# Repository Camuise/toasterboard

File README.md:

# Toasterboard

My attempt at making an open-source Breadboard Companion-like dev board.

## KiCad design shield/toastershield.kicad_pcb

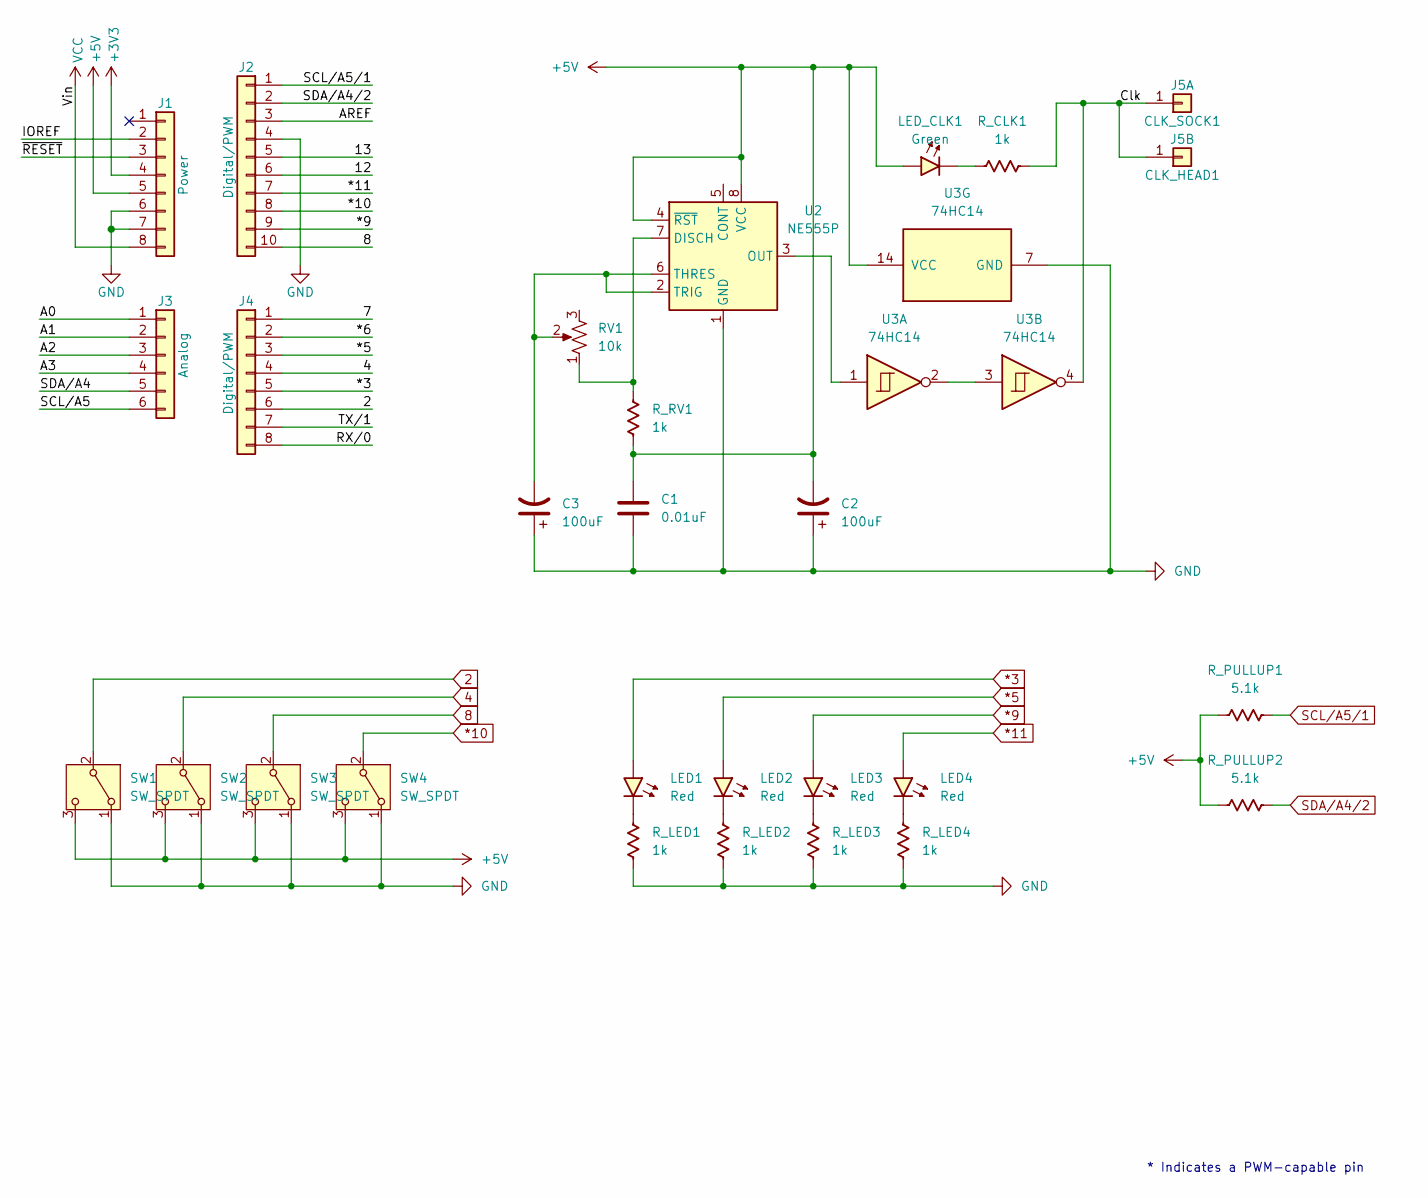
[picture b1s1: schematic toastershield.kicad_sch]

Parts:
C1: 0.01uF; C_Disc_D5.0mm_W2.5mm_P5.00mm
C2, C3: 100uF; CP_Radial_D5.0mm_P2.00mm
CLK_HEAD1: J5B; PinHeader_1x01_P2.54mm_Vertical
CLK_SOCK1: J5A; PinSocket_1x01_P2.54mm_Vertical
J1: Power; PinSocket_1x08_P2.54mm_Vertical
J2: Digital/PWM; PinSocket_1x10_P2.54mm_Vertical
J3: Analog; PinSocket_1x06_P2.54mm_Vertical
J4: Digital/PWM; PinSocket_1x08_P2.54mm_Vertical
LED1, LED2, LED3, LED4: Red; LED_D3.0mm
LED_CLK1: Green; LED_D3.0mm
RV1: 10k; Potentiometer_Piher_PT-15-V02_Vertical
R_CLK1: 1k; R_Axial_DIN0207_L6.3mm_D2.5mm_P2.54mm_Vertical
R_LED1, R_LED2, R_LED3, R_LED4: 1k; R_Axial_DIN0207_L6.3mm_D2.5mm_P2.54mm_Vertical
R_PULLUP1, R_PULLUP2: 5.1k; R_Axial_DIN0207_L6.3mm_D2.5mm_P2.54mm_Vertical
R_RV1: 1k; R_Axial_DIN0207_L6.3mm_D2.5mm_P5.08mm_Vertical
SW1, SW2, SW3, SW4: SW_SPDT; SW_Slide_SPDT_Straight_CK_OS102011MS2Q
U2: NE555P; DIP-8_W7.62mm_Socket
U3: 74HC14; DIP-14_W7.62mm_Socket

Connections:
2: J4.6, SW1.2 (B)
4: J4.4, SW2.2 (B)
8: J2.10, SW3.2 (B)
*3: J4.5, LED1.2 (A)
*5: J4.3, LED2.2 (A)
*9: J2.9, LED3.2 (A)
*10: J2.8, SW4.2 (B)
*11: J2.7, LED4.2 (A)
+3V3: J1.4
+5V: C1.1, C2.2, J1.5, LED_CLK1.2 (A), R_PULLUP1.1, R_PULLUP2.1, R_RV1.2, SW1.3 (C), SW2.3 (C), SW3.3 (C), SW4.3 (C), U2.4 (~RST), U2.8 (VCC), U3.14 (VCC)
/7: J4.1
/12: J2.6
/13: J2.5
/*6: J4.2
/A0: J3.1
/A1: J3.2
/A2: J3.3
/A3: J3.4
/AREF: J2.3
/Clk: CLK_HEAD1.1 (Pin_1_1), CLK_SOCK1.1 (Pin_1_1), R_CLK1.2, U3.4
/IOREF: J1.2
/RX/0: J4.8
/SCL/A5: J3.6
/SDA/A4: J3.5
/TX/1: J4.7
/~RESET: J1.3
GND: C1.2, C2.1, C3.1, J1.6, J1.7, J2.4, R_LED1.2, R_LED2.2, R_LED3.2, R_LED4.2, SW1.1 (A), SW2.1 (A), SW3.1 (A), SW4.1 (A), U2.1 (GND), U3.7 (GND)
unnamed: LED1.1 (K), R_LED1.1
unnamed: LED2.1 (K), R_LED2.1
unnamed: LED3.1 (K), R_LED3.1
unnamed: LED4.1 (K), R_LED4.1
unnamed: LED_CLK1.1 (K), R_CLK1.1
unnamed: RV1.1, R_RV1.1, U2.7 (DISCH)
unnamed: U2.3 (OUT), U3.1
unnamed: C3.2, RV1.2, U2.2 (TRIG), U2.6 (THRES)
unnamed: U3.2, U3.3
SCL/A5/1: J2.1, R_PULLUP1.2
SDA/A4/2: J2.2, R_PULLUP2.2
VCC: J1.8

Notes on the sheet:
* Indicates a PWM-capable pin

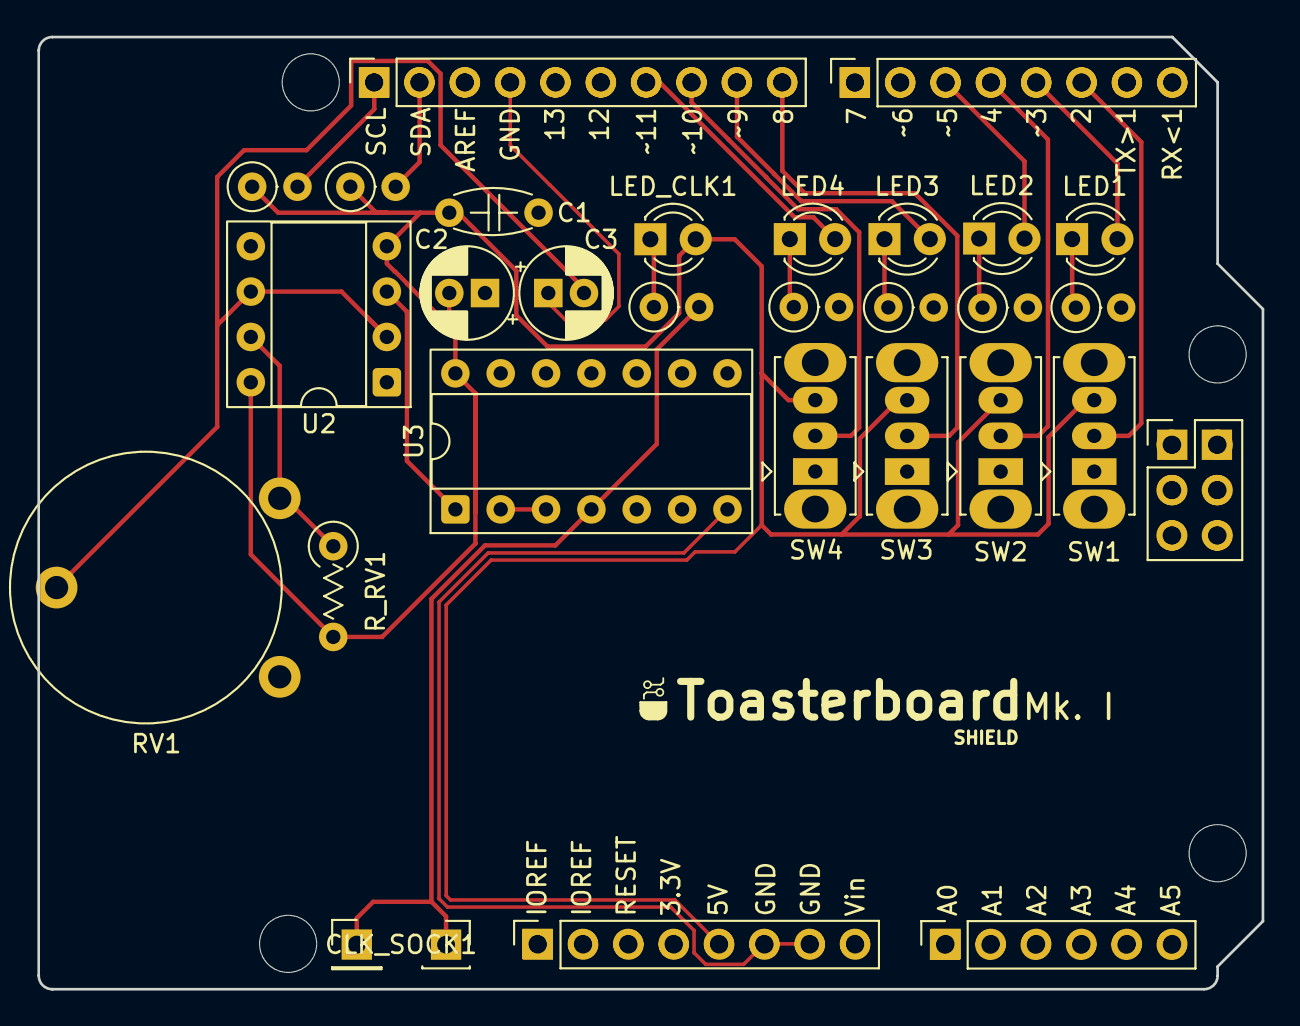
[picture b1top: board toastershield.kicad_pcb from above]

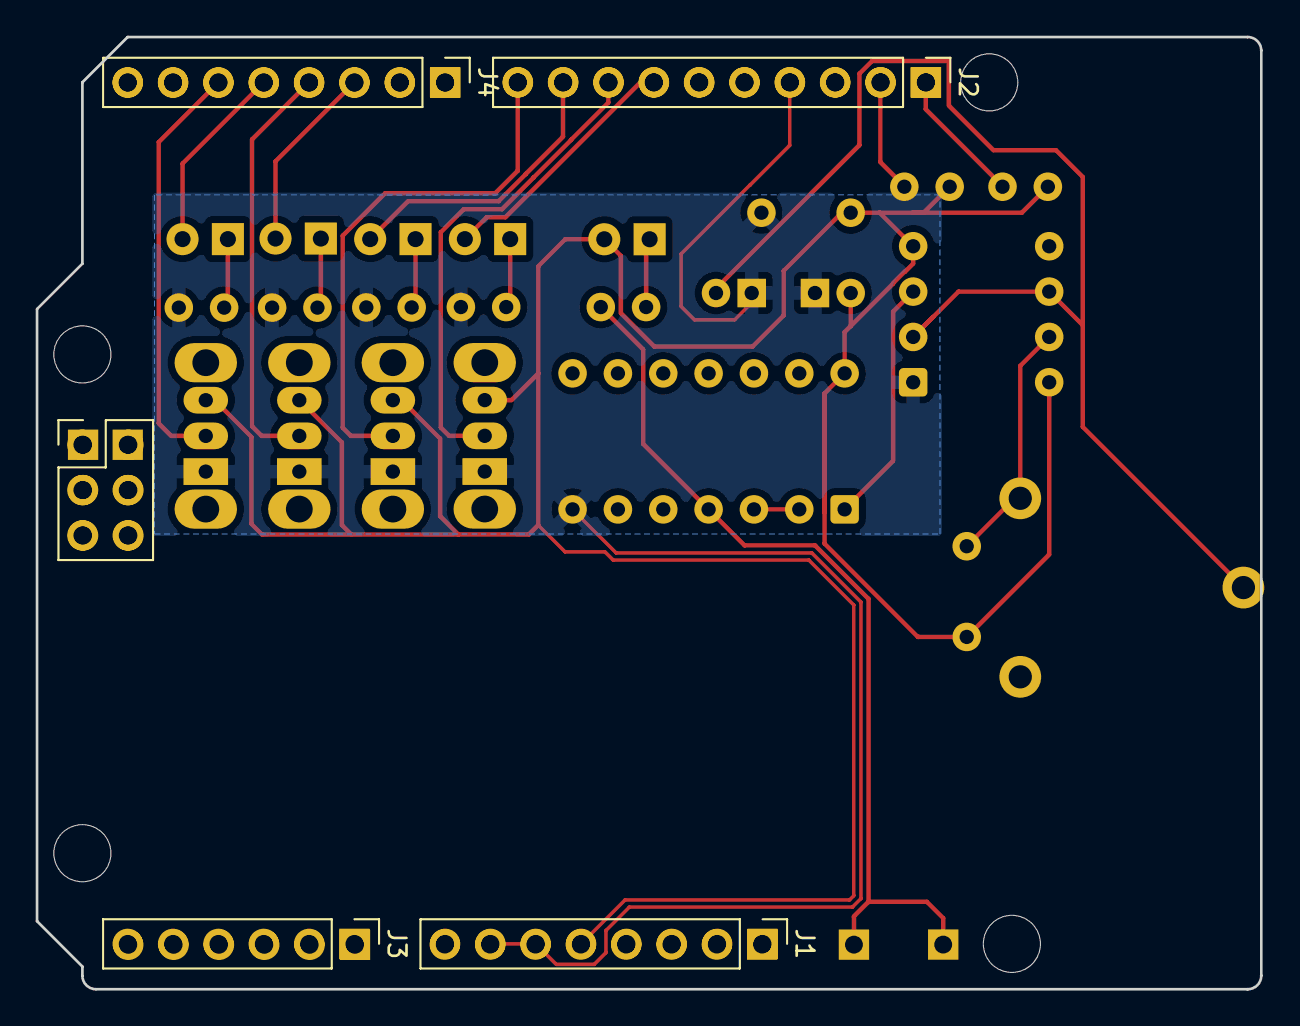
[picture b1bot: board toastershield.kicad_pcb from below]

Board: 2 copper layers, 68.6 x 53.3 mm, 39 parts (5 on the bottom side), 22 nets.

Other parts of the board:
J5: PinHeader_2x03_P2.54mm_Vertical
JB1, JB4: PinSocket_1x08_P2.54mm_Vertical
JB2: PinSocket_1x10_P2.54mm_Vertical
JB3: PinSocket_1x06_P2.54mm_Vertical
JB5: PinHeader_2x03_P2.54mm_Vertical
MH1, MH2, MH3, MH4: MountingHole_3.2mm

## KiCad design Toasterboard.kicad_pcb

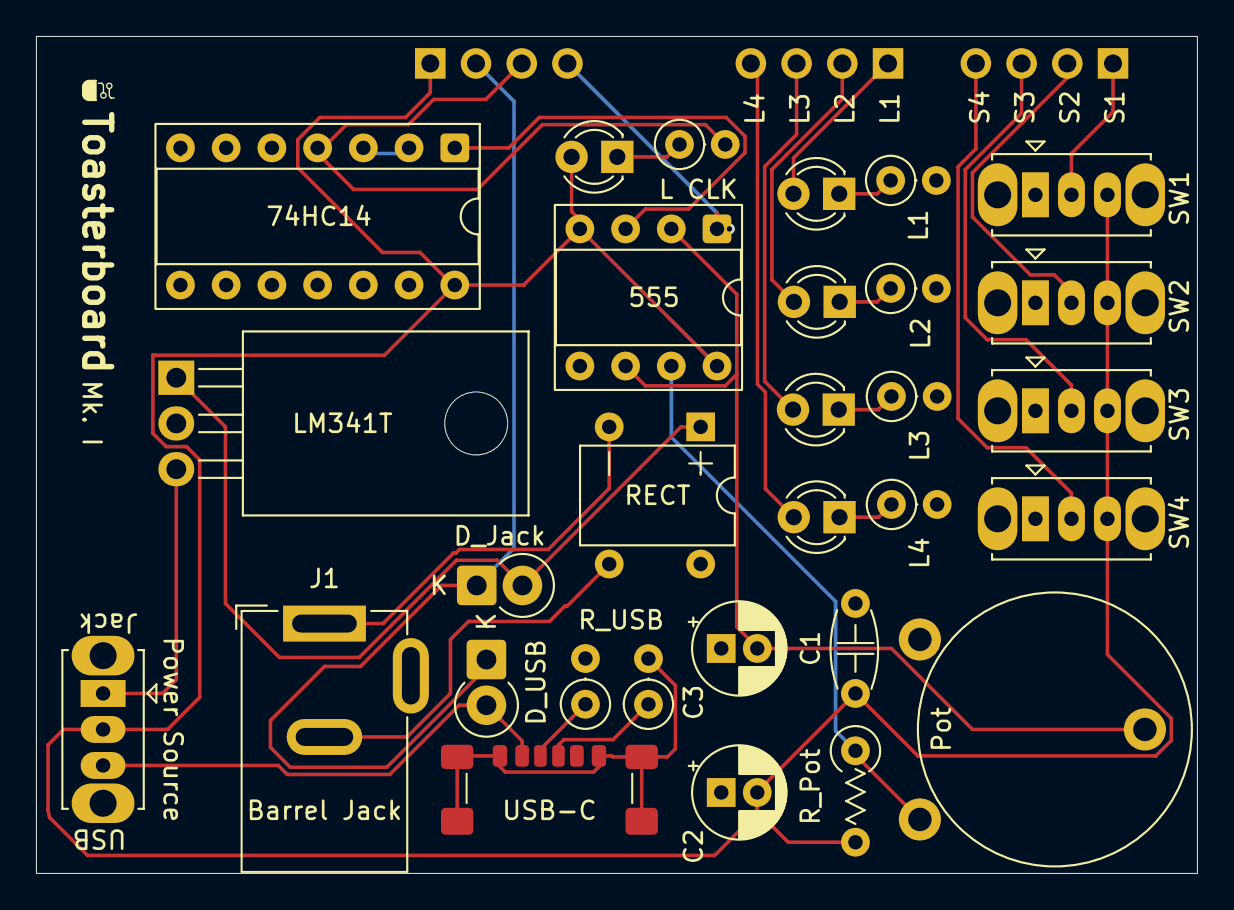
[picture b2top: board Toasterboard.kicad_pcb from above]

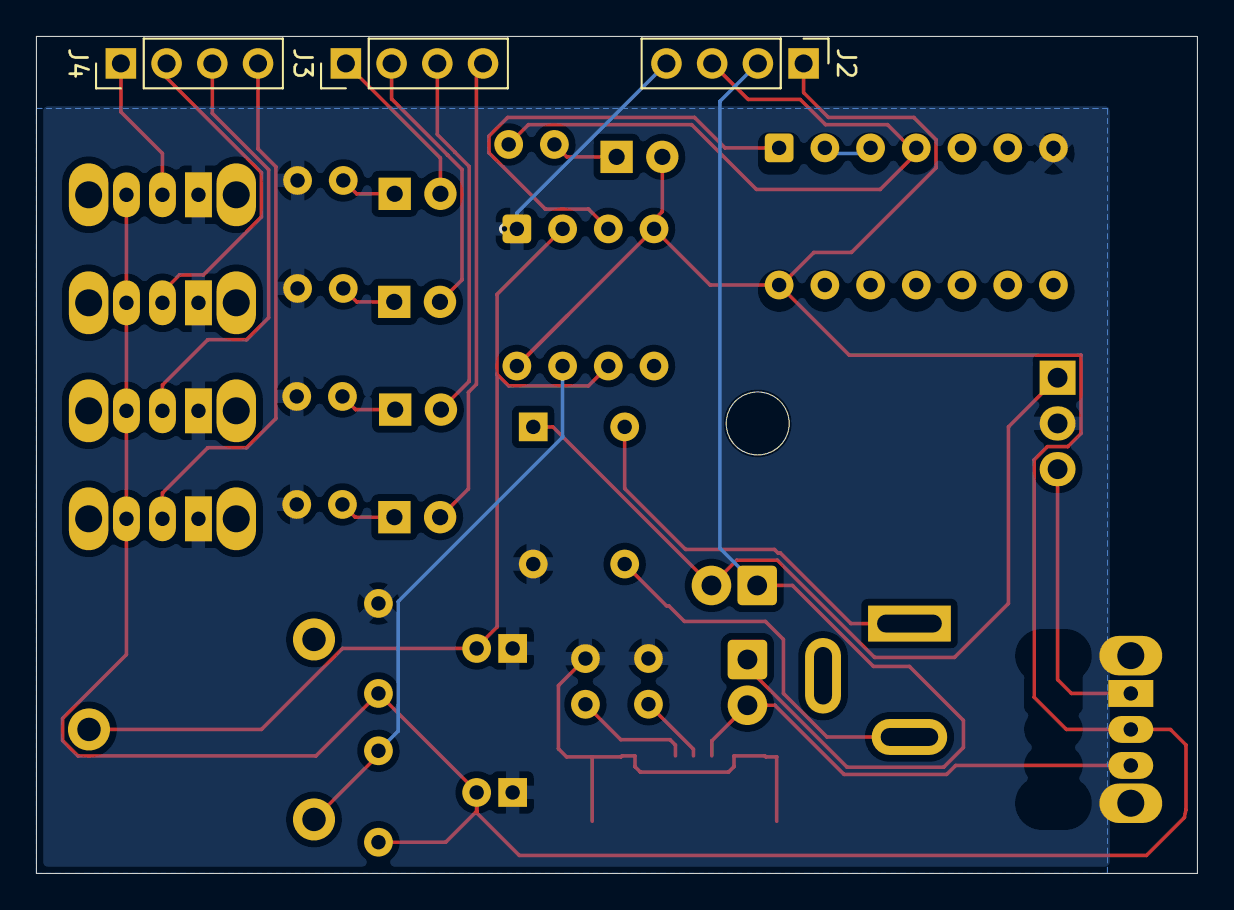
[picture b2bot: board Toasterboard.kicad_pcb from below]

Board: 2 copper layers, 64.5 x 46.5 mm, 33 parts (3 on the bottom side), 28 nets.

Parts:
74HC14: 74HC14; DIP-14_W7.62mm_Socket
555: NE555P; DIP-8_W7.62mm_Socket
C1: 0.01uF; C_Disc_D5.0mm_W2.5mm_P5.00mm
C2, C3: 100uF; CP_Radial_D5.0mm_P2.00mm
D_Jack: 1N5817; D_DO-41_SOD81_P2.54mm_Vertical_CathodeUp
D_USB: 1N5817; D_DO-41_SOD81_P2.54mm_Vertical_CathodeUp
J1: Barrel Jack; BarrelJack_GCT_DCJ200-10-A_Horizontal
J2: Power; PinHeader_1x04_P2.54mm_Vertical
J3: LEDs; PinHeader_1x04_P2.54mm_Vertical
J4: Switches; PinHeader_1x04_P2.54mm_Vertical
L1, L2, L3, L4: Red; LED_D3.0mm
L CLK: Green; LED_D3.0mm
LM341T: LM341T-05_TO220; TO-220-3_Horizontal_TabDown
RECT: CS10D; Diode_Bridge_DIP-4_W7.62mm_P5.08mm
RV1: 10k; Potentiometer_Piher_PT-15-V02_Vertical
R_CLK1: 1k; R_Axial_DIN0207_L6.3mm_D2.5mm_P2.54mm_Vertical
R_LED1, R_LED2, R_LED3, R_LED4: 1k; R_Axial_DIN0207_L6.3mm_D2.5mm_P2.54mm_Vertical
R_Pot: 1k; R_Axial_DIN0207_L6.3mm_D2.5mm_P5.08mm_Vertical
R_USB1, R_USB2: 5.1k; R_Axial_DIN0207_L6.3mm_D2.5mm_P2.54mm_Vertical
SW1, SW2, SW3, SW4: SW_SPDT; SW_Slide_SPDT_Straight_CK_OS102011MS2Q
SW_PWR1: SW_SPDT; SW_Slide_SPDT_Straight_CK_OS102011MS2Q
USB-C: USB_C_Plug_USB2.0; USB_C_Receptacle_GCT_USB4135-GF-A_6P_TopMnt_Horizontal

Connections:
+5V: 74HC14.14 (VCC), 555.4 (~RST), 555.8 (VCC), C1.1, C2.2, J2.1, L CLK.2 (A), R_Pot.2, SW1.3 (C), SW2.3 (C), SW3.3 (C), SW4.3 (C), SW_PWR1.2 (B)
+VDC: D_Jack.1 (K), D_USB.1 (K), J2.2
/Clk: 74HC14.4, J2.3, R_CLK1.2
GND: 74HC14.7 (GND), 555.1 (GND), C1.2, C2.1, C3.1, J2.4, LM341T.2 (GND), RECT.4 (2), R_LED1.2, R_LED2.2, R_LED3.2, R_LED4.2, R_USB1.2, R_USB2.2, SW1.1 (A), SW2.1 (A), SW3.1 (A), SW4.1 (A), USB-C.A12 (GND), USB-C.B12 (GND), USB-C.SH (SHIELD)
unnamed: D_Jack.2 (A), LM341T.1 (VI), RECT.1 (+)
unnamed: J1.1, RECT.2 (1)
unnamed: J1.2, RECT.3 (-)
unnamed: D_USB.2 (A), SW_PWR1.3 (C), USB-C.A9 (VBUS), USB-C.B9 (VBUS)
unnamed: J3.1, L1.2 (A)
unnamed: J3.2, L2.2 (A)
unnamed: J3.3, L3.2 (A)
unnamed: J3.4, L4.2 (A)
unnamed: J4.1, SW1.2 (B)
unnamed: J4.2, SW2.2 (B)
unnamed: J4.3, SW3.2 (B)
unnamed: J4.4, SW4.2 (B)
unnamed: L1.1 (K), R_LED1.1
unnamed: L2.1 (K), R_LED2.1
unnamed: L3.1 (K), R_LED3.1
unnamed: L4.1 (K), R_LED4.1
unnamed: L CLK.1 (K), R_CLK1.1
unnamed: R_USB1.1, USB-C.A5 (CC)
unnamed: R_USB2.1, USB-C.B5 (VCONN)
unnamed: LM341T.3 (VO), SW_PWR1.1 (A)
unnamed: 555.7 (DISCH), RV1.1, R_Pot.1
unnamed: 74HC14.1, 555.3 (OUT)
unnamed: 555.2 (TRIG), 555.6 (THRES), C3.2, RV1.2
unnamed: 74HC14.2, 74HC14.3

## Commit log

2026-05-15 init: new kicad project
2026-05-16 feat: a proper readme
2026-05-16 FORGE: update journal
2026-05-16 feat: schematic progress! switches and leds done
2026-05-16 FORGE: add may 15 journal entry
2026-05-16 FORGE: fix to match format
2026-05-16 FORGE: fix broken image embeds
2026-05-16 FORGE: use pngs
2026-05-16 FORGE: may 16 - start!
2026-05-16 FORGE: i forgot to switch the image links to png...
2026-05-16 feat: finished basic logics
2026-05-16 FORGE: new journal
2026-05-17 feat: finish routing
2026-05-17 FORGE: new journal entry
2026-05-17 FORGE: fix may 16 img links
2026-05-17 feat: make board more compact, add branding
2026-05-17 FORGE: may 17 journal
2026-05-17 chore: move standalone board to own dir
2026-05-18 feat: add shield version of board
2026-05-18 FORGE: add journal entry!
2026-05-18 feat: i2c pullups on the shield
2026-05-18 feat: fix text and pins
2026-05-18 FORGE: fix broken images
